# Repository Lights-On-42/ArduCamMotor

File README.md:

# ArduCamMotor
Arduino Projekt um 8 Motor Treiber und eine Arducam auf ein Board zusammen zusteuern

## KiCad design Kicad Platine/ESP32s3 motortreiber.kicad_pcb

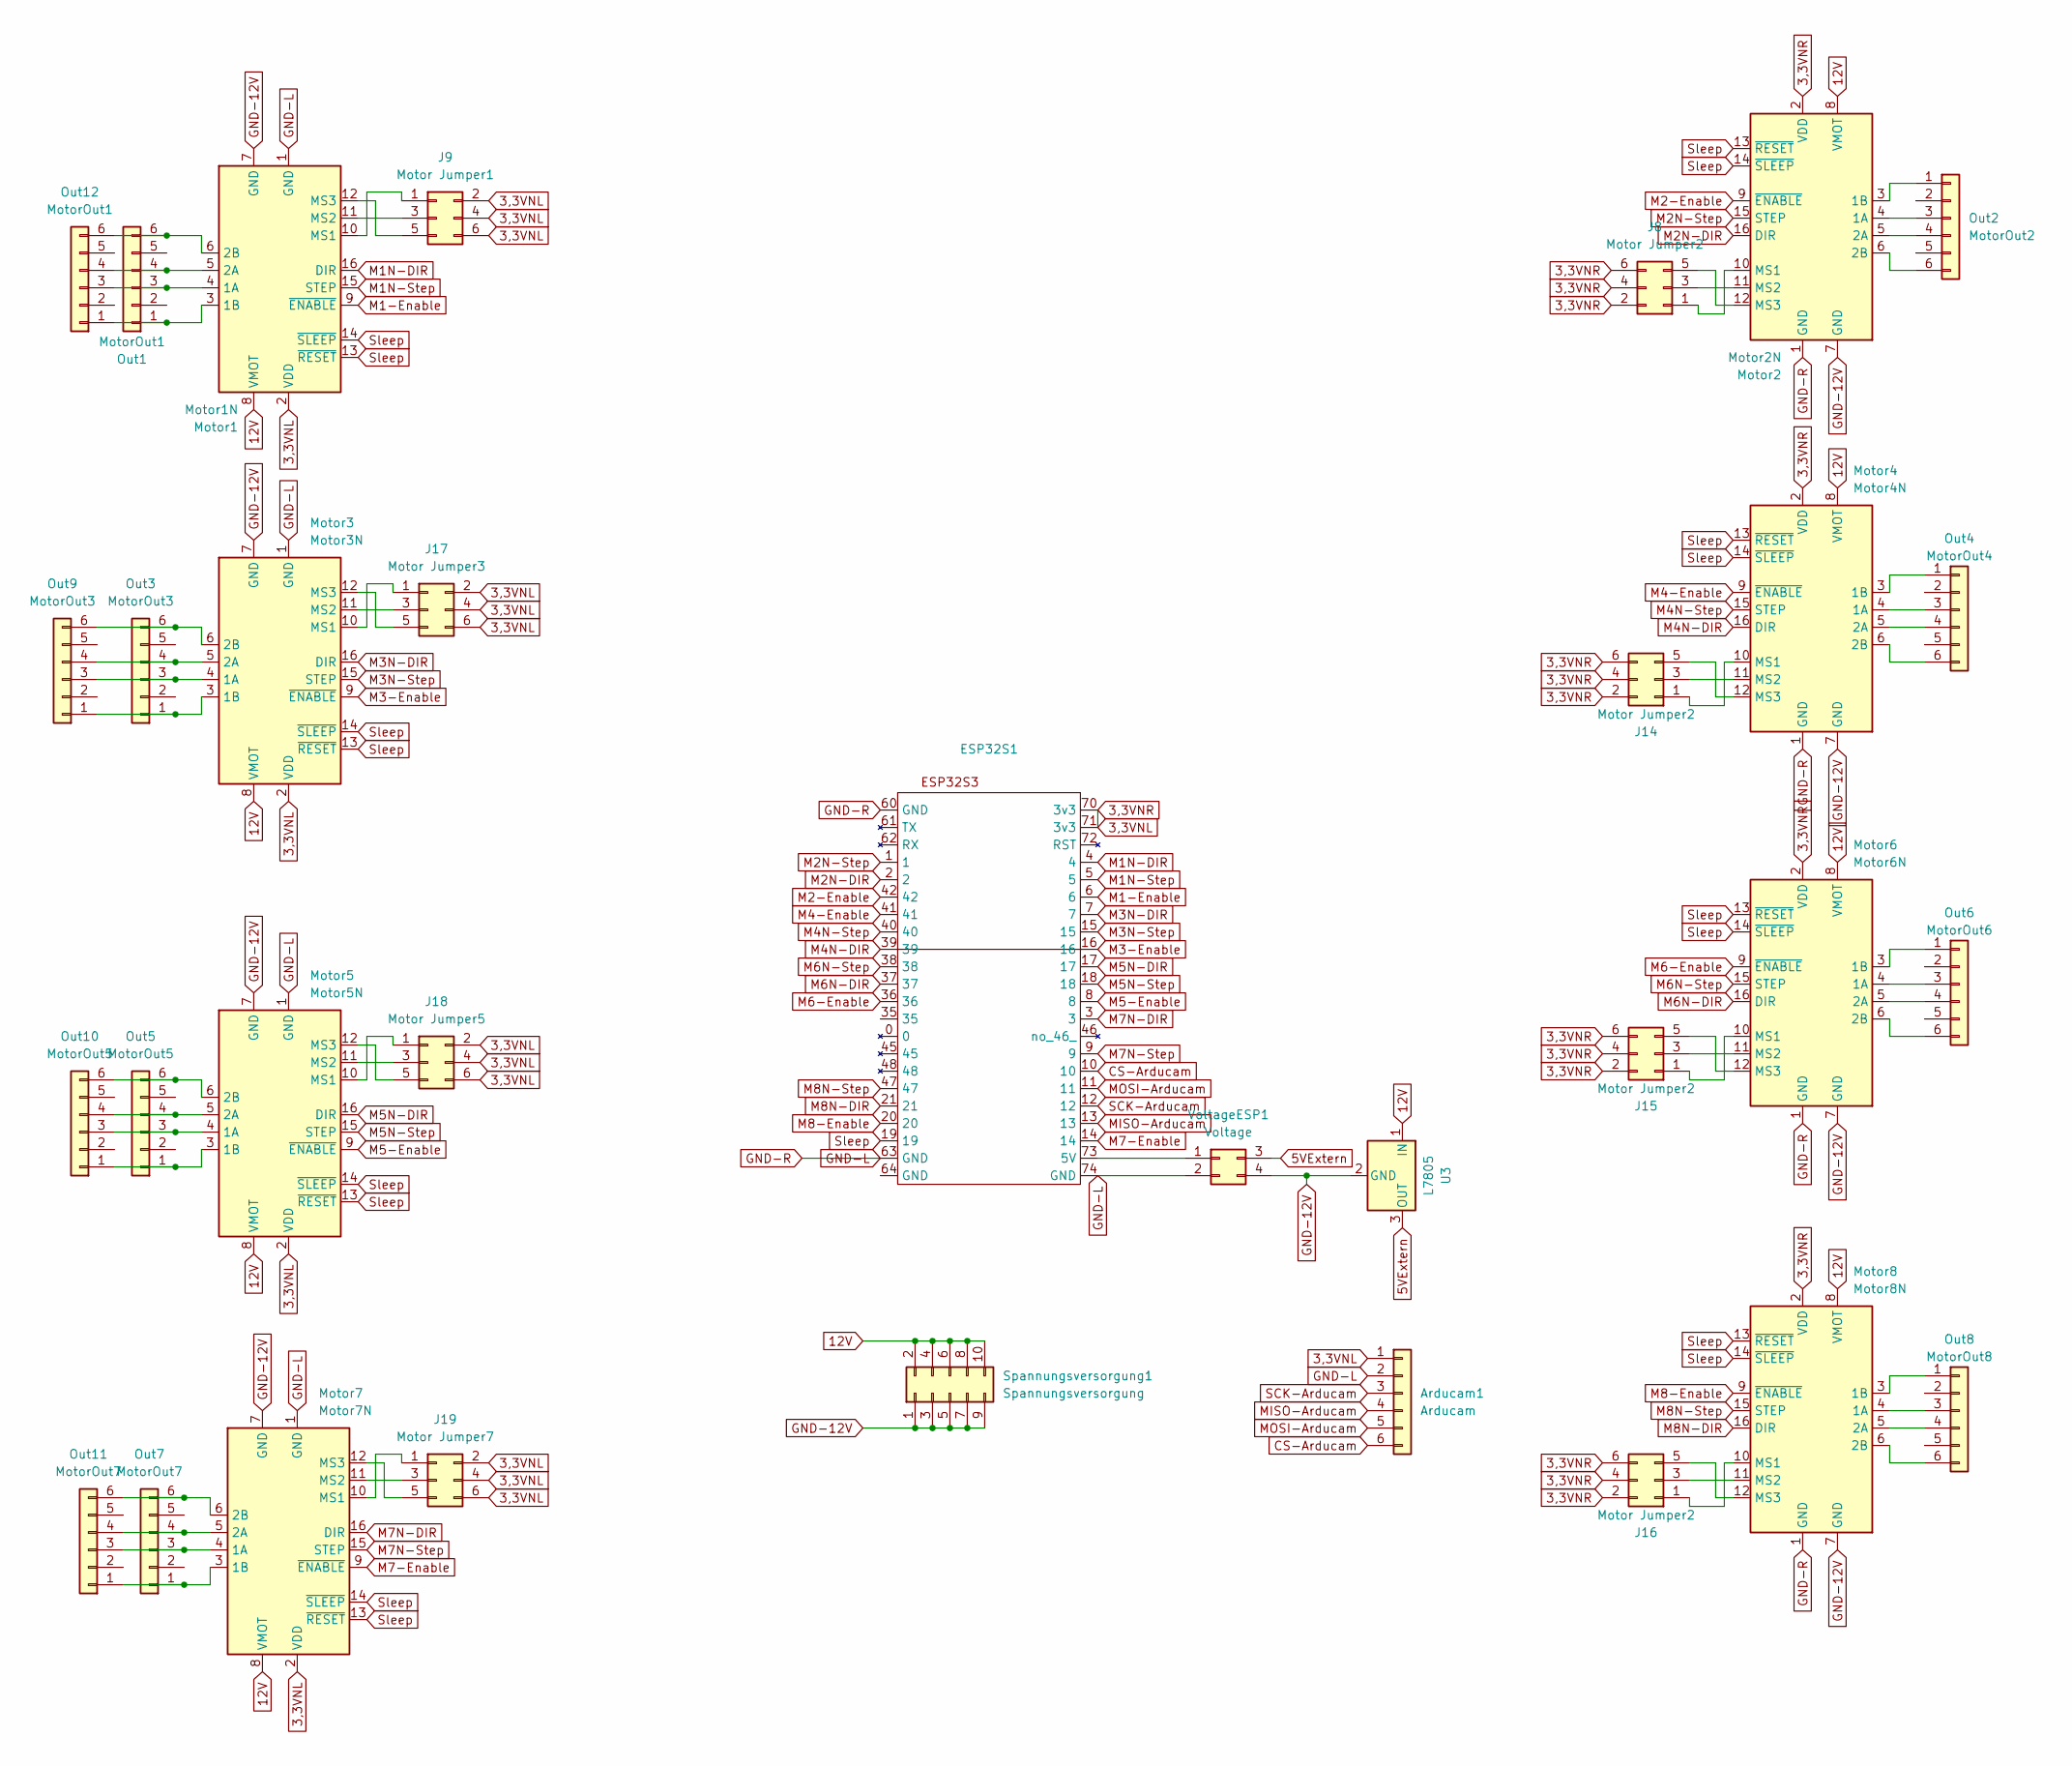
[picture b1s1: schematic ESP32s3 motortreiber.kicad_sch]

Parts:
Arducam1: Arducam; PinHeader_1x06_P2.54mm_Vertical
ESP32S1: esp32s3
J8, J14, J15, J16: Motor Jumper2; PinHeader_2x03_P2.54mm_Vertical
J9: Motor Jumper1; PinHeader_2x03_P2.54mm_Vertical
J17: Motor Jumper3; PinHeader_2x03_P2.54mm_Vertical
J18: Motor Jumper5; PinHeader_2x03_P2.54mm_Vertical
J19: Motor Jumper7; PinHeader_2x03_P2.54mm_Vertical
Motor1: Motor1N; Pololu_Breakout-16_15.2x20.3mm
Motor2: Motor2N; Pololu_Breakout-16_15.2x20.3mm
Motor3: Motor3N; Pololu_Breakout-16_15.2x20.3mm
Motor4: Motor4N; Pololu_Breakout-16_15.2x20.3mm
Motor5: Motor5N; Pololu_Breakout-16_15.2x20.3mm
Motor6: Motor6N; Pololu_Breakout-16_15.2x20.3mm
Motor7: Motor7N; Pololu_Breakout-16_15.2x20.3mm
Motor8: Motor8N; Pololu_Breakout-16_15.2x20.3mm
Out1, Out12: MotorOut1; PinHeader_1x06_P2.00mm_Vertical
Out2: MotorOut2; PinHeader_1x06_P2.00mm_Vertical
Out3, Out9: MotorOut3; PinHeader_1x06_P2.00mm_Vertical
Out4: MotorOut4; PinHeader_1x06_P2.00mm_Vertical
Out5, Out10: MotorOut5; PinHeader_1x06_P2.00mm_Vertical
Out6: MotorOut6; PinHeader_1x06_P2.00mm_Vertical
Out7, Out11: MotorOut7; PinHeader_1x06_P2.00mm_Vertical
Out8: MotorOut8; PinHeader_1x06_P2.00mm_Vertical
Spannungsversorgung1: Spannungsversorgung; PinHeader_2x05_P2.54mm_Vertical
U3: L7805; TO-220-3_Vertical
VoltageESP1: Voltage; PinHeader_2x02_P2.54mm_Vertical

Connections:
3,3VNL: Arducam1.1, ESP32S1.70 (3v3), ESP32S1.71 (3v3), J8.2, J8.4, J8.6, J9.2, J9.4, J9.6, J14.2, J14.4, J14.6, J15.2, J15.4, J15.6, J16.2, J16.4, J16.6, J17.2, J17.4, J17.6, J18.2, J18.4, J18.6, J19.2, J19.4, J19.6, Motor1.2 (VDD), Motor2.2 (VDD), Motor3.2 (VDD), Motor4.2 (VDD), Motor5.2 (VDD), Motor6.2 (VDD), Motor7.2 (VDD), Motor8.2 (VDD)
5VExtern: U3.3 (OUT), VoltageESP1.3
12V: Motor1.8 (VMOT), Motor2.8 (VMOT), Motor3.8 (VMOT), Motor4.8 (VMOT), Motor5.8 (VMOT), Motor6.8 (VMOT), Motor7.8 (VMOT), Motor8.8 (VMOT), Spannungsversorgung1.2, Spannungsversorgung1.4, Spannungsversorgung1.6, Spannungsversorgung1.8, Spannungsversorgung1.10, U3.1 (IN)
CS-Arducam: Arducam1.6, ESP32S1.10
GND-12V: Motor1.7 (GND), Motor2.7 (GND), Motor3.7 (GND), Motor4.7 (GND), Motor5.7 (GND), Motor6.7 (GND), Motor7.7 (GND), Motor8.7 (GND), Spannungsversorgung1.1, Spannungsversorgung1.3, Spannungsversorgung1.5, Spannungsversorgung1.7, Spannungsversorgung1.9, U3.2 (GND), VoltageESP1.4
GND-L: Arducam1.2, ESP32S1.60 (GND), ESP32S1.63 (GND), ESP32S1.74 (GND), Motor1.1 (GND), Motor2.1 (GND), Motor3.1 (GND), Motor4.1 (GND), Motor5.1 (GND), Motor6.1 (GND), Motor7.1 (GND), Motor8.1 (GND), VoltageESP1.2
M1-Enable: ESP32S1.6, Motor1.9 (~ENABLE)
M1N-DIR: ESP32S1.4, Motor1.16 (DIR)
M1N-Step: ESP32S1.5, Motor1.15 (STEP)
M2-Enable: ESP32S1.42, Motor2.9 (~ENABLE)
M2N-DIR: ESP32S1.2, Motor2.16 (DIR)
M2N-Step: ESP32S1.1, Motor2.15 (STEP)
M3-Enable: ESP32S1.16, Motor3.9 (~ENABLE)
M3N-DIR: ESP32S1.7, Motor3.16 (DIR)
M3N-Step: ESP32S1.15, Motor3.15 (STEP)
M4-Enable: ESP32S1.41, Motor4.9 (~ENABLE)
M4N-DIR: ESP32S1.39, Motor4.16 (DIR)
M4N-Step: ESP32S1.40, Motor4.15 (STEP)
M5-Enable: ESP32S1.8, Motor5.9 (~ENABLE)
M5N-DIR: ESP32S1.17, Motor5.16 (DIR)
M5N-Step: ESP32S1.18, Motor5.15 (STEP)
M6-Enable: ESP32S1.36, Motor6.9 (~ENABLE)
M6N-DIR: ESP32S1.37, Motor6.16 (DIR)
M6N-Step: ESP32S1.38, Motor6.15 (STEP)
M7-Enable: ESP32S1.14, Motor7.9 (~ENABLE)
M7N-DIR: ESP32S1.3, Motor7.16 (DIR)
M7N-Step: ESP32S1.9, Motor7.15 (STEP)
M8-Enable: ESP32S1.20, Motor8.9 (~ENABLE)
M8N-DIR: ESP32S1.21, Motor8.16 (DIR)
M8N-Step: ESP32S1.47, Motor8.15 (STEP)
MISO-Arducam: Arducam1.4, ESP32S1.13
MOSI-Arducam: Arducam1.5, ESP32S1.11
unnamed: ESP32S1.73 (5V), VoltageESP1.1
unnamed: J8.1, Motor2.10 (MS1)
unnamed: J8.3, Motor2.11 (MS2)
unnamed: J8.5, Motor2.12 (MS3)
unnamed: J9.1, Motor1.10 (MS1)
unnamed: J9.3, Motor1.11 (MS2)
unnamed: J9.5, Motor1.12 (MS3)
unnamed: J14.1, Motor4.10 (MS1)
unnamed: J14.3, Motor4.11 (MS2)
unnamed: J14.5, Motor4.12 (MS3)
unnamed: J15.1, Motor6.10 (MS1)
unnamed: J15.3, Motor6.11 (MS2)
unnamed: J15.5, Motor6.12 (MS3)
unnamed: J16.1, Motor8.10 (MS1)
unnamed: J16.3, Motor8.11 (MS2)
unnamed: J16.5, Motor8.12 (MS3)
unnamed: J17.1, Motor3.10 (MS1)
unnamed: J17.3, Motor3.11 (MS2)
unnamed: J17.5, Motor3.12 (MS3)
unnamed: J18.1, Motor5.10 (MS1)
unnamed: J18.3, Motor5.11 (MS2)
unnamed: J18.5, Motor5.12 (MS3)
unnamed: J19.1, Motor7.10 (MS1)
unnamed: J19.3, Motor7.11 (MS2)
unnamed: J19.5, Motor7.12 (MS3)
unnamed: Motor1.4 (1A), Out1.3, Out12.3
unnamed: Motor1.3 (1B), Out1.1, Out12.1
unnamed: Motor1.5 (2A), Out1.4, Out12.4
unnamed: Motor1.6 (2B), Out1.6, Out12.6
unnamed: Motor2.4 (1A), Out2.3
unnamed: Motor2.3 (1B), Out2.1
unnamed: Motor2.5 (2A), Out2.4
unnamed: Motor2.6 (2B), Out2.6
unnamed: Motor3.4 (1A), Out3.3, Out9.3
unnamed: Motor3.3 (1B), Out3.1, Out9.1
unnamed: Motor3.5 (2A), Out3.4, Out9.4
unnamed: Motor3.6 (2B), Out3.6, Out9.6
unnamed: Motor4.4 (1A), Out4.3
unnamed: Motor4.3 (1B), Out4.1
unnamed: Motor4.5 (2A), Out4.4
unnamed: Motor4.6 (2B), Out4.6
unnamed: Motor5.4 (1A), Out5.3, Out10.3
unnamed: Motor5.3 (1B), Out5.1, Out10.1
unnamed: Motor5.5 (2A), Out5.4, Out10.4
unnamed: Motor5.6 (2B), Out5.6, Out10.6
unnamed: Motor6.4 (1A), Out6.3
unnamed: Motor6.3 (1B), Out6.1
unnamed: Motor6.5 (2A), Out6.4
unnamed: Motor6.6 (2B), Out6.6
unnamed: Motor7.4 (1A), Out7.3, Out11.3
unnamed: Motor7.3 (1B), Out7.1, Out11.1
unnamed: Motor7.5 (2A), Out7.4, Out11.4
unnamed: Motor7.6 (2B), Out7.6, Out11.6
unnamed: Motor8.4 (1A), Out8.3
unnamed: Motor8.3 (1B), Out8.1
unnamed: Motor8.5 (2A), Out8.4
unnamed: Motor8.6 (2B), Out8.6
SCK-Arducam: Arducam1.3, ESP32S1.12
Sleep: ESP32S1.19, Motor1.13 (~RESET), Motor1.14 (~SLEEP), Motor2.13 (~RESET), Motor2.14 (~SLEEP), Motor3.13 (~RESET), Motor3.14 (~SLEEP), Motor4.13 (~RESET), Motor4.14 (~SLEEP), Motor5.13 (~RESET), Motor5.14 (~SLEEP), Motor6.13 (~RESET), Motor6.14 (~SLEEP), Motor7.13 (~RESET), Motor7.14 (~SLEEP), Motor8.13 (~RESET), Motor8.14 (~SLEEP)

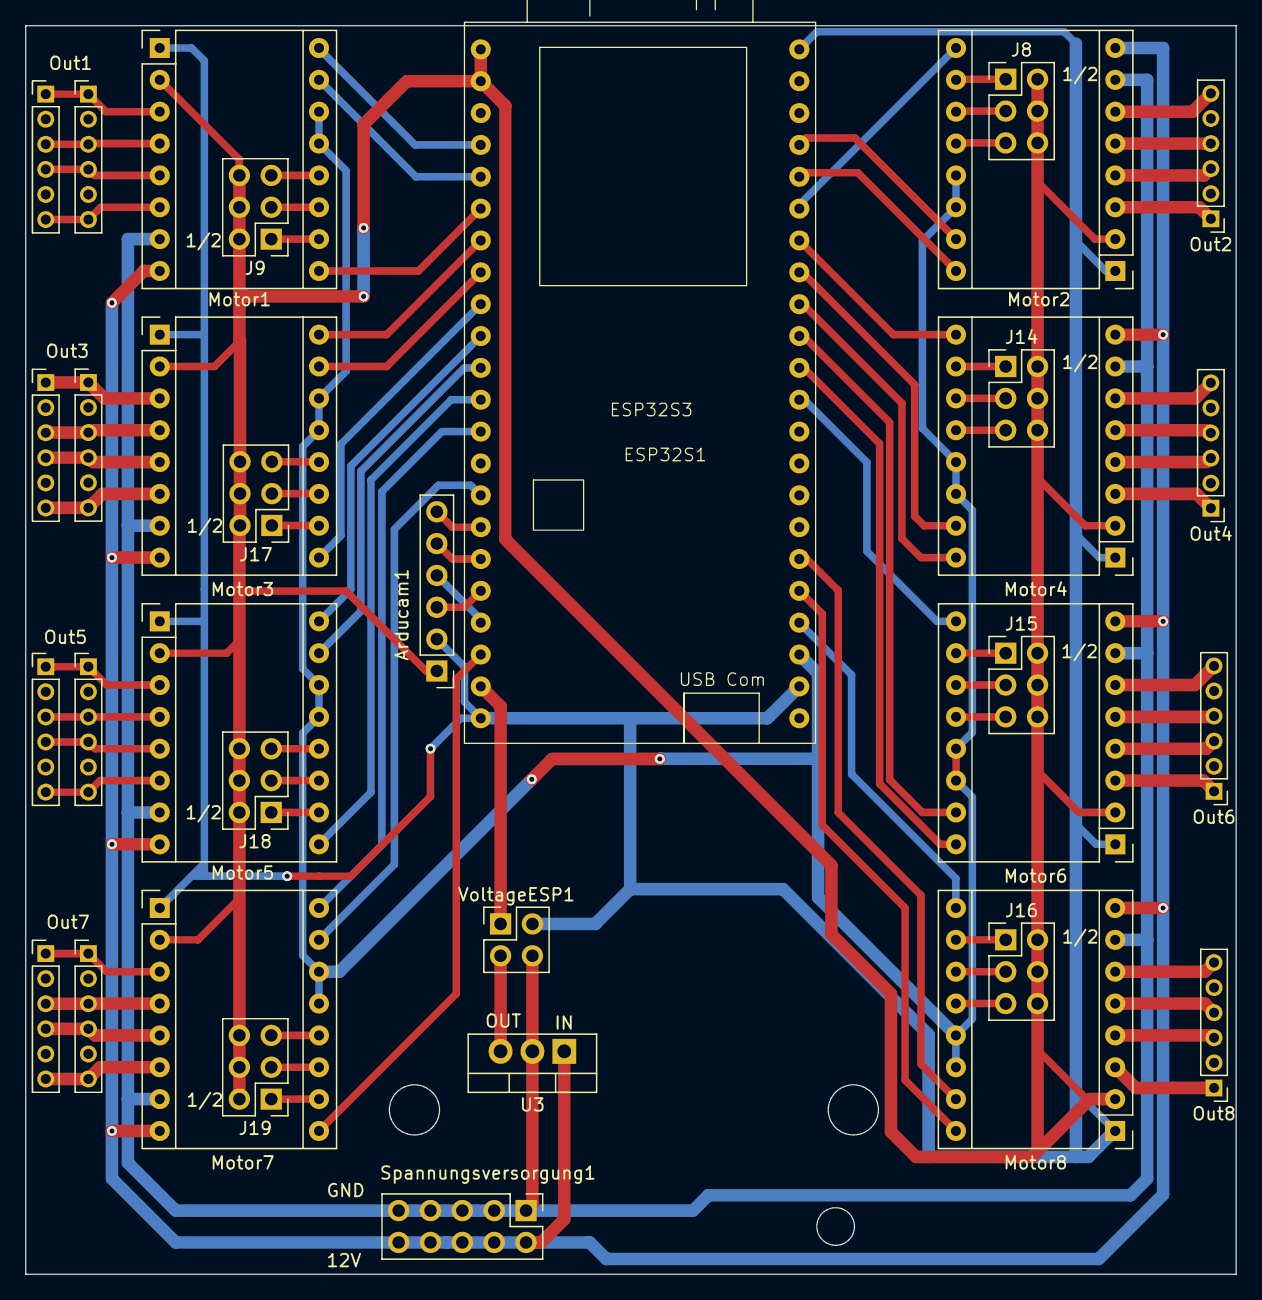
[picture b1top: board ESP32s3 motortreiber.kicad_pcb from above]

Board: 2 copper layers, 96.5 x 99.6 mm, 33 parts (0 on the bottom side), 91 nets.

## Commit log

2025-01-06 Erste StartVersion mal schauen o alles hoch geht
2025-03-31 Einbau das über das we interface testpins geschickt werden können Zusatzliche Funktion für testParameter im Ino file erste Test mit dem P4 Ideen eingebaut um Camera über socket zu senden funktioniert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
